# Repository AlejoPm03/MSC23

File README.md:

# Transformar MSC23 em sensor de tensão para a bateria

1. Soldar a placa normalmente usando o projeto que esta na branch voltage_sensor, 
não soldar compnentes que estão com X vermelho no esquematico

2. Soldar o conector na camada inversa a do projeto com as duas pernas centrais isoladas e distanciadas dos pads. 
Na proxima imagem tem exemplo, é recomendavel colocar algo para isolar o pino do pad (talvez o fenolite de uma PCB)

Deberia ficar algo parecido com a imagem:

3. No proximo passo serão soldados os componentes selecionados em montagem aerea

Deveria ficar algo parecido com a imagem:

# Documentos de Referência
[Simulação](design/analog_voltage_sensor.asc)
[Esquemático](exports/schematic.pdf/)

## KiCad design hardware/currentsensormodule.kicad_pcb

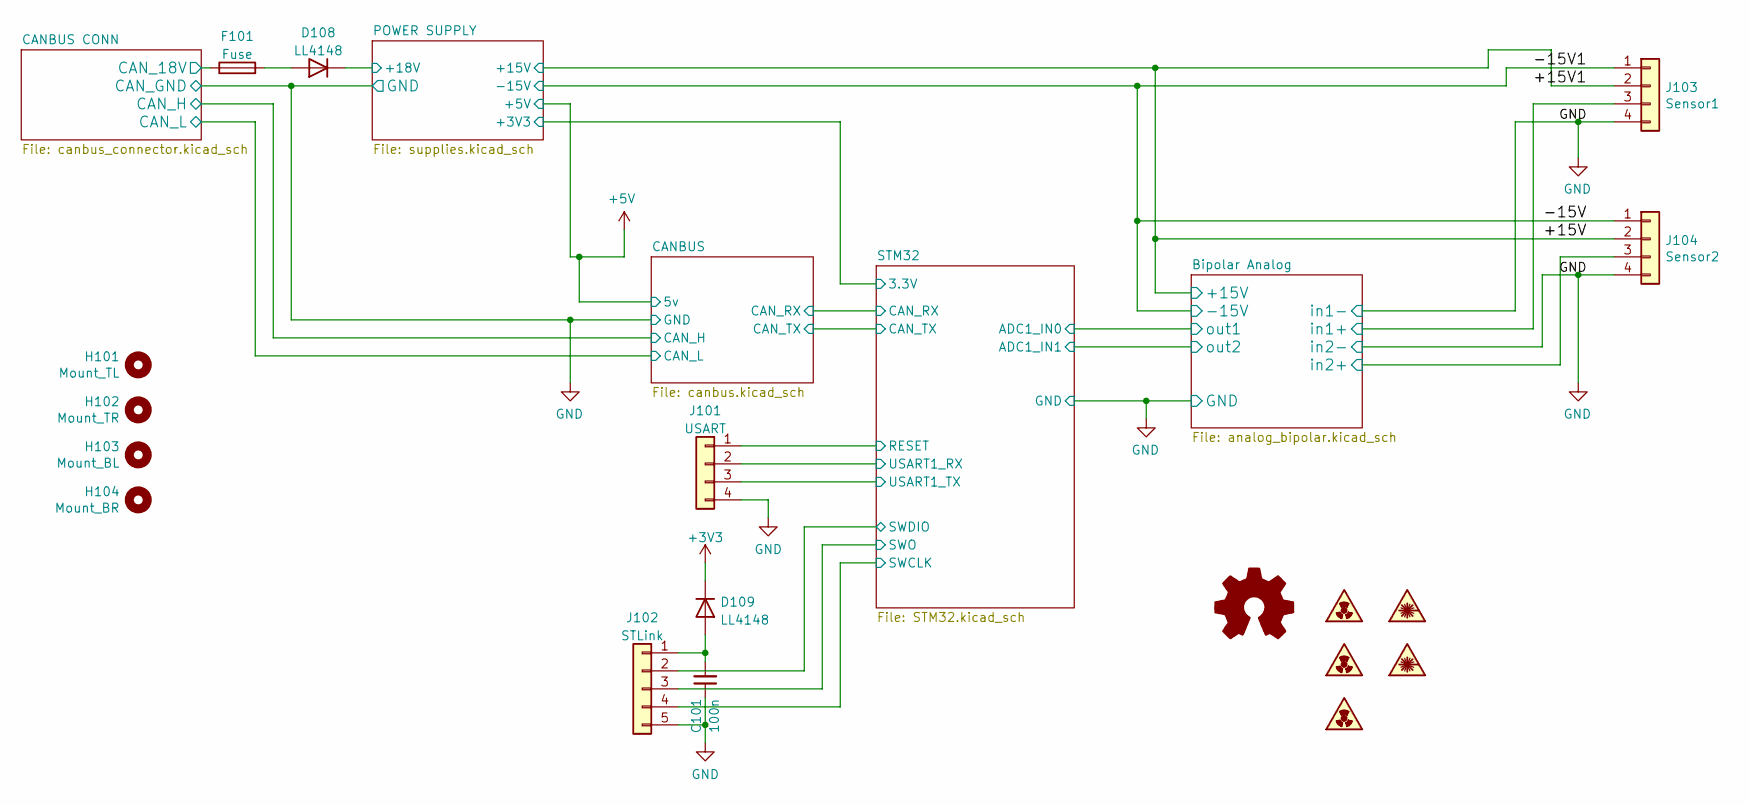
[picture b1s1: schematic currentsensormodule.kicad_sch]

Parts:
C101: 100n; C_0603_1608Metric_Pad1.08x0.95mm_HandSolder
D108, D109: LL4148; D_MiniMELF
F101: Fuse; Fuse_1812_4532Metric_Pad1.30x3.40mm_HandSolder
H101: Mount_TL; MountingHole_3.2mm_M3
H102: Mount_TR; MountingHole_3.2mm_M3
H103: Mount_BL; MountingHole_3.2mm_M3
H104: Mount_BR; MountingHole_3.2mm_M3
J101: USART; PinHeader_1x04_P2.54mm_Vertical_SMD_Pin1Left
J102: STLink; PinHeader_1x05_P2.54mm_Vertical_SMD_Pin1Left
J103: Sensor1; PhoenixContact_MSTBA_2,5_4-G-5,08_1x04_P5.08mm_Horizontal
J104: Sensor2; PhoenixContact_MSTBA_2,5_4-G-5,08_1x04_P5.08mm_Horizontal
LOGO101: Logo_Open_Hardware_Small; OSHW-Logo2_7.3x6mm_SilkScreen
SYM101, SYM103: SYM_Radioactive_Radiation_Small; symbol_logoZenite
SYM102, SYM104: SYM_LASER_Small; synbol_logoifsc
SYM105: SYM_Radioactive_Radiation_Small; symbol_naolavar

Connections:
+3V3: D109.1 (K); also elsewhere on the board
+15V: J103.2, J104.2; also elsewhere on the board
-15V: J103.1, J104.1; also elsewhere on the board
/Bipolar Analog/in1+: J103.3; also elsewhere on the board
/Bipolar Analog/in2+: J104.3; also elsewhere on the board
/CANBUS CONN/CAN_18V: F101.1; also elsewhere on the board
/POWER SUPPLY/+18V: D108.1 (K); also elsewhere on the board
/STM32/RESET: J101.1; also elsewhere on the board
/STM32/SWCLK: J102.4; also elsewhere on the board
/STM32/SWDIO: J102.2; also elsewhere on the board
/STM32/SWO: J102.3; also elsewhere on the board
/STM32/USART1_RX: J101.2; also elsewhere on the board
/STM32/USART1_TX: J101.3; also elsewhere on the board
GND: C101.1, J101.4, J102.5, J103.4, J104.4; also elsewhere on the board
unnamed: C101.2, D109.2 (A), J102.1
unnamed: D108.2 (A), F101.2

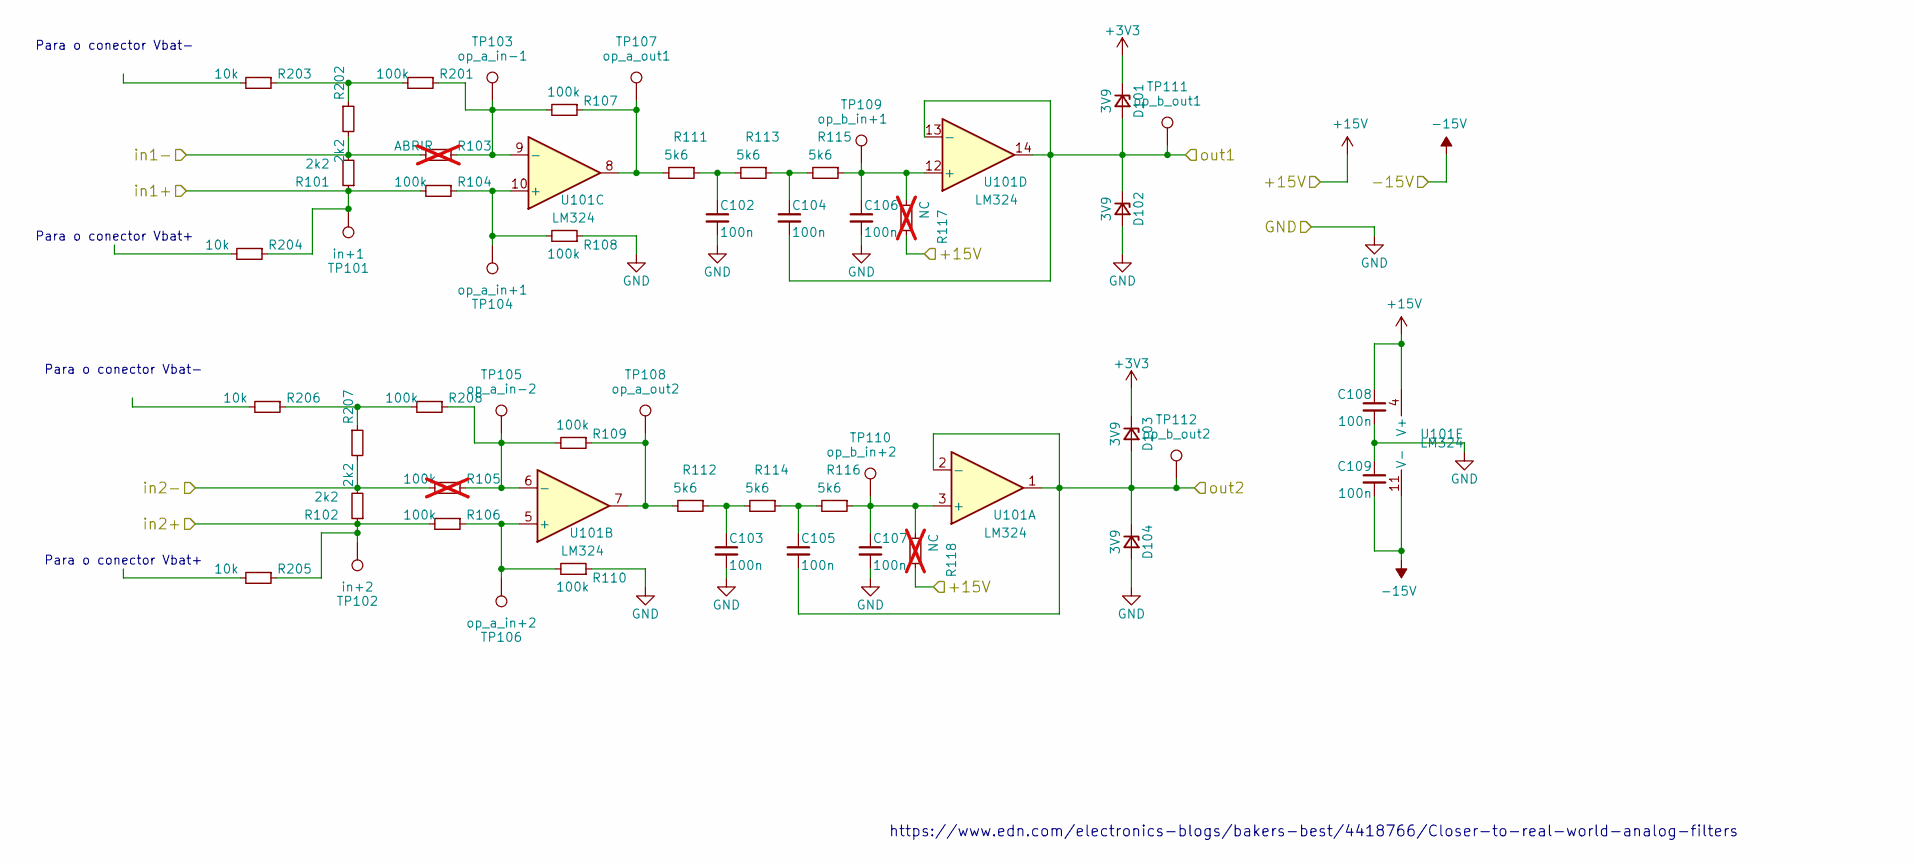
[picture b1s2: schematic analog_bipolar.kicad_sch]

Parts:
C102, C103, C104, C105, C106, C107, C108, C109: 100n; C_0603_1608Metric_Pad1.08x0.95mm_HandSolder
D101, D102, D103, D104: 3V9; D_MiniMELF_Handsoldering
R101, R102, R202, R207: 2k2; R_0603_1608Metric_Pad0.98x0.95mm_HandSolder
R103: ABRIR; R_0603_1608Metric_Pad0.98x0.95mm_HandSolder; not fitted
R104, R106, R107, R108, R109, R110, R201, R208: 100k; R_0603_1608Metric_Pad0.98x0.95mm_HandSolder
R105: 100k; R_0603_1608Metric_Pad0.98x0.95mm_HandSolder; not fitted
R111, R112, R113, R114, R115, R116: 5k6; R_0603_1608Metric_Pad0.98x0.95mm_HandSolder
R117, R118: NC; R_0603_1608Metric_Pad0.98x0.95mm_HandSolder; not fitted
R203, R204, R205, R206: 10k; R_0603_1608Metric_Pad0.98x0.95mm_HandSolder
TP101: in+1; TestPoint_Pad_2.0x2.0mm
TP102: in+2; TestPoint_Pad_2.0x2.0mm
TP103: op_a_in-1; TestPoint_Pad_2.0x2.0mm
TP104: op_a_in+1; TestPoint_Pad_2.0x2.0mm
TP105: op_a_in-2; TestPoint_Pad_2.0x2.0mm
TP106: op_a_in+2; TestPoint_Pad_2.0x2.0mm
TP107: op_a_out1; TestPoint_Pad_2.0x2.0mm
TP108: op_a_out2; TestPoint_Pad_2.0x2.0mm
TP109: op_b_in+1; TestPoint_Pad_2.0x2.0mm
TP110: op_b_in+2; TestPoint_Pad_2.0x2.0mm
TP111: op_b_out1; TestPoint_Pad_2.0x2.0mm
TP112: op_b_out2; TestPoint_Pad_2.0x2.0mm
U101: LM324; SOIC-14_3.9x8.7mm_P1.27mm

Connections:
+3V3: D101.1 (K), D103.1 (K); also elsewhere on the board
+15V: C108.1, R117.1, R118.1, U101.4 (V+); also elsewhere on the board
-15V: C109.2, U101.11 (V-); also elsewhere on the board
/Bipolar Analog/in1+: R101.1, R104.2, R204.1, TP101.1; also elsewhere on the board
/Bipolar Analog/in2+: R102.1, R106.2, R205.1, TP102.1; also elsewhere on the board
/Bipolar Analog/out1: C104.2, D101.2 (A), D102.1 (K), TP111.1, U101.13 (-), U101.14; also elsewhere on the board
/Bipolar Analog/out2: C105.2, D103.2 (A), D104.1 (K), TP112.1, U101.1, U101.2 (-); also elsewhere on the board
GND: C102.2, C103.2, C106.2, C107.2, C108.2, C109.1, D102.2 (A), D104.2 (A), R101.2, R102.2, R103.2, R105.2, R108.1, R110.1, R202.2, R207.2; also elsewhere on the board
unnamed: C102.1, R111.1, R113.2
unnamed: C103.1, R112.1, R114.2
unnamed: C104.1, R113.1, R115.2
unnamed: C105.1, R114.1, R116.2
unnamed: C106.1, R115.1, R117.2, TP109.1, U101.12 (+)
unnamed: C107.1, R116.1, R118.2, TP110.1, U101.3 (+)
unnamed: R103.1, R107.2, R201.1, TP103.1, U101.9 (-)
unnamed: R104.1, R108.2, TP104.1, U101.10 (+)
unnamed: R105.1, R109.2, R208.1, TP105.1, U101.6 (-)
unnamed: R106.1, R110.2, TP106.1, U101.5 (+)
unnamed: R107.1, R111.2, TP107.1, U101.8
unnamed: R109.1, R112.2, TP108.1, U101.7
unnamed: R201.2, R202.1, R203.1
unnamed: R206.1, R207.1, R208.2

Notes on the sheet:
Para o conector Vbat-
Para o conector Vbat+
https://www.edn.com/electronics-blogs/bakers-best/4418766/Closer-to-real-world-analog-filters

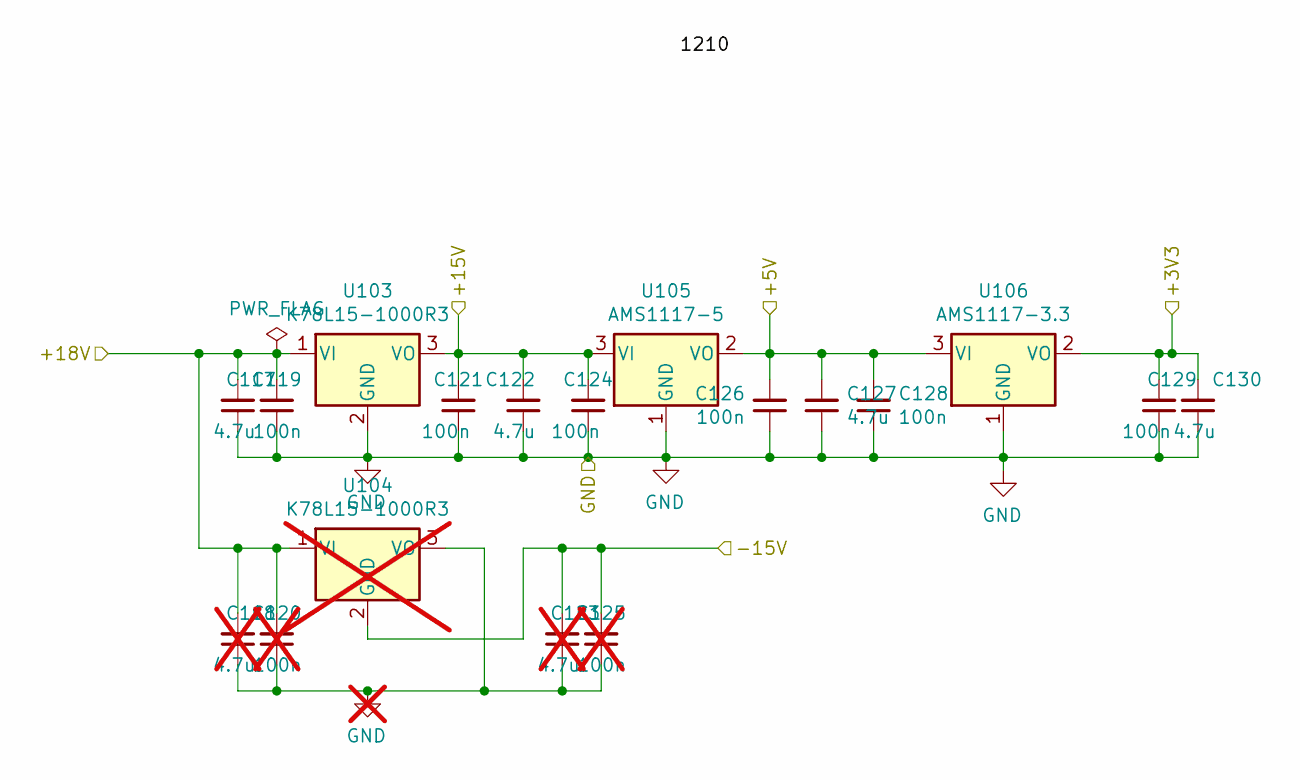
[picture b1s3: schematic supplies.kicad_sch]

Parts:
C117, C122, C127, C130: 4.7u; C_1206_3216Metric_Pad1.33x1.80mm_HandSolder
C118, C123: 4.7u; C_1206_3216Metric_Pad1.33x1.80mm_HandSolder; not fitted
C119, C121, C124, C126, C128, C129: 100n; C_0603_1608Metric_Pad1.08x0.95mm_HandSolder
C120, C125: 100n; C_0603_1608Metric_Pad1.08x0.95mm_HandSolder; not fitted
U103: K78L15-1000R3; TO-220-3_Horizontal_Tabless_SMD
U104: K78L15-1000R3; TO-220-3_Horizontal_Tabless_SMD; not fitted
U105: AMS1117-5; SOT-223-3_TabPin2
U106: AMS1117-3.3; SOT-223-3_TabPin2

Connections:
+3V3: C129.2, C130.2, U106.2 (VO); also elsewhere on the board
+5V: C126.2, C127.2, C128.2, U105.2 (VO), U106.3 (VI); also elsewhere on the board
+15V: C121.2, C122.2, C124.2, U103.3 (VO), U105.3 (VI); also elsewhere on the board
-15V: C123.2, C125.2, U104.2 (GND); also elsewhere on the board
/POWER SUPPLY/+18V: C117.2, C118.2, C119.2, C120.2, U103.1 (VI), U104.1 (VI); also elsewhere on the board
GND: C117.1, C118.1, C119.1, C120.1, C121.1, C122.1, C123.1, C124.1, C125.1, C126.1, C127.1, C128.1, C129.1, C130.1, U103.2 (GND), U104.3 (VO), U105.1 (GND), U106.1 (GND); also elsewhere on the board

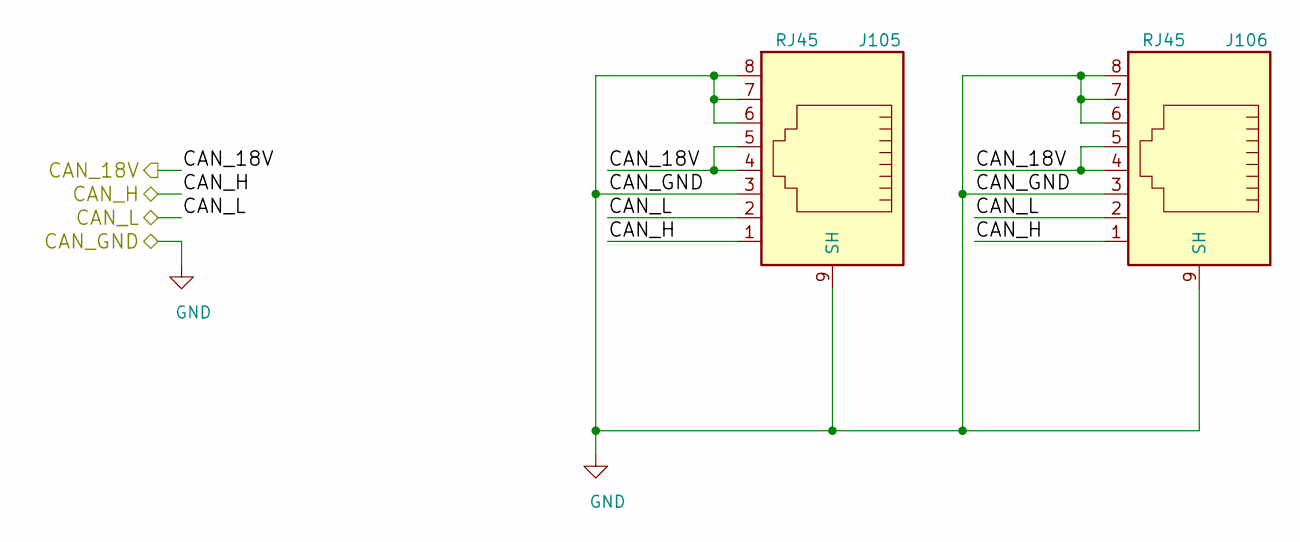
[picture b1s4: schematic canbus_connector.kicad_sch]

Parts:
J105, J106: RJ45; RJ45_YH59_01

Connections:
/CANBUS CONN/CAN_18V: J105.4, J105.5, J106.4, J106.5; also elsewhere on the board
/CANBUS CONN/CAN_H: J105.1, J106.1; also elsewhere on the board
/CANBUS CONN/CAN_L: J105.2, J106.2; also elsewhere on the board
GND: J105.3, J105.6, J105.7, J105.8, J105.9 (SH), J106.3, J106.6, J106.7, J106.8, J106.9 (SH); also elsewhere on the board

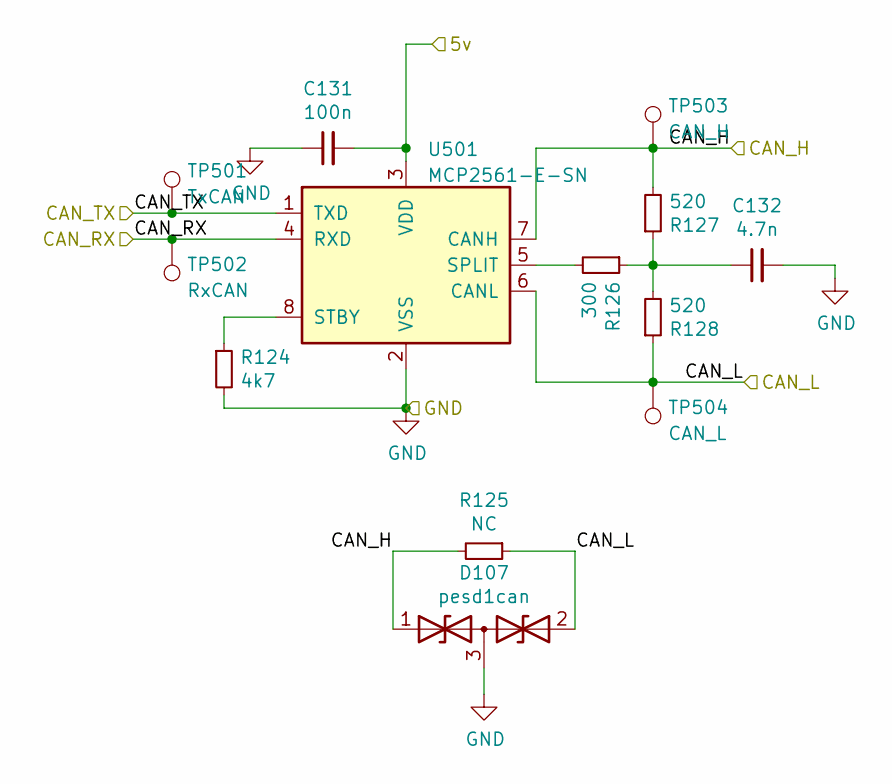
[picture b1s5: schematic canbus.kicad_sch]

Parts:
C131: 100n; C_0603_1608Metric_Pad1.08x0.95mm_HandSolder
C132: 4.7n; C_0603_1608Metric_Pad1.08x0.95mm_HandSolder
D107: pesd1can; SOT-23
R124: 4k7; R_0603_1608Metric_Pad0.98x0.95mm_HandSolder
R125: NC; R_0603_1608Metric_Pad0.98x0.95mm_HandSolder
R126: 300; R_0603_1608Metric_Pad0.98x0.95mm_HandSolder
R127, R128: 520; R_0603_1608Metric_Pad0.98x0.95mm_HandSolder
TP501: TxCAN; TestPoint_Pad_2.0x2.0mm
TP502: RxCAN; TestPoint_Pad_2.0x2.0mm
TP503: CAN_H; TestPoint_Pad_2.0x2.0mm
TP504: CAN_L; TestPoint_Pad_2.0x2.0mm
U501: MCP2561-E-SN; SOIC-8_3.9x4.9mm_P1.27mm

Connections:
+5V: C131.2, U501.3 (VDD); also elsewhere on the board
/CANBUS CONN/CAN_H: D107.1 (A1), R125.2, R127.2, TP503.1, U501.7 (CANH); also elsewhere on the board
/CANBUS CONN/CAN_L: D107.2 (A2), R125.1, R128.1, TP504.1, U501.6 (CANL); also elsewhere on the board
/CANBUS/CAN_RX: TP502.1, U501.4 (RXD); also elsewhere on the board
/CANBUS/CAN_TX: TP501.1, U501.1 (TXD); also elsewhere on the board
GND: C131.1, C132.2, D107.3 (common), R124.2, U501.2 (VSS); also elsewhere on the board
unnamed: C132.1, R126.1, R127.1, R128.2
unnamed: R124.1, U501.8 (STBY)
unnamed: R126.2, U501.5 (SPLIT)

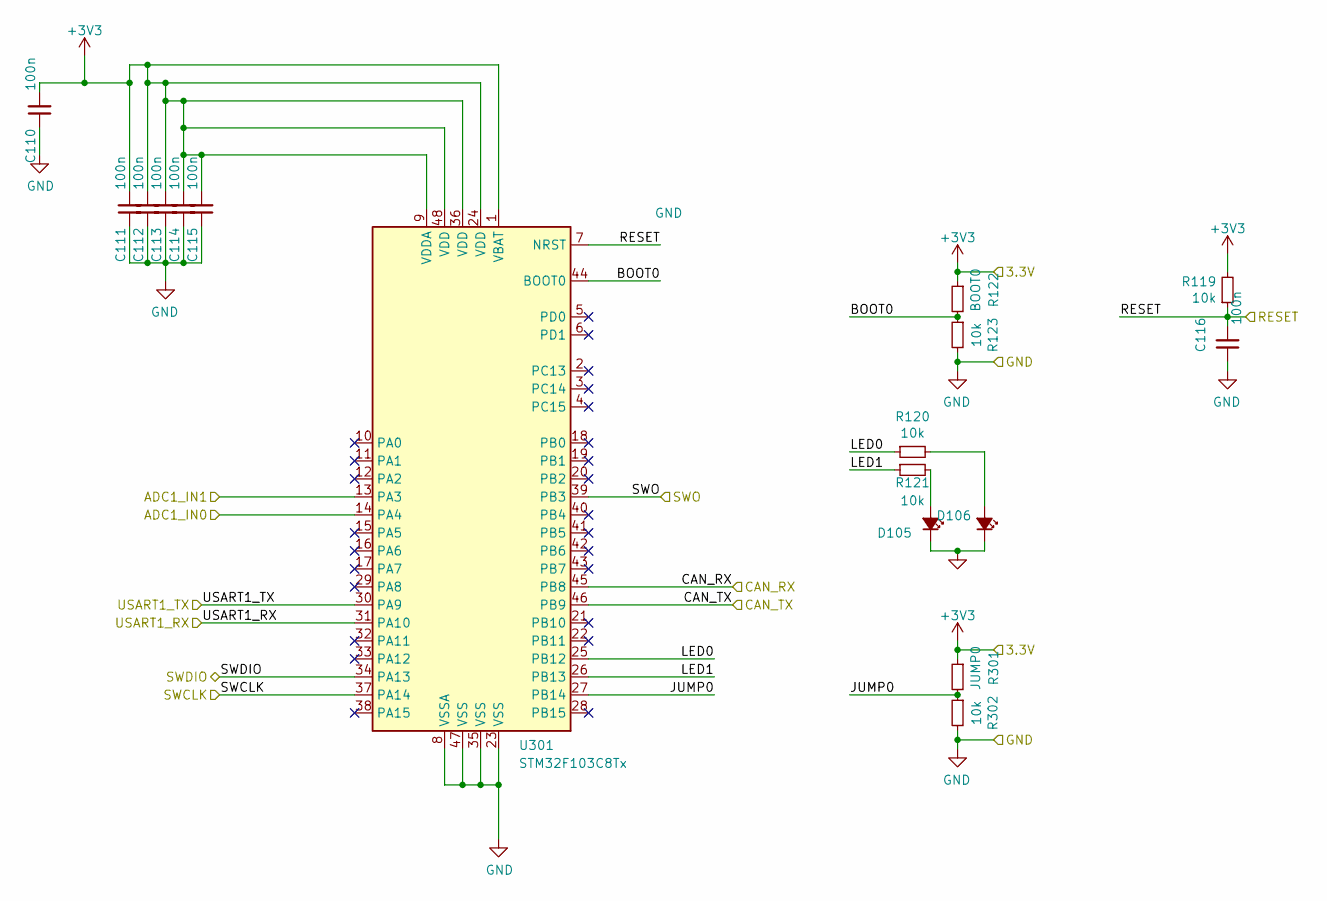
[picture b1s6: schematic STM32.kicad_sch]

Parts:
C110, C111, C112, C113, C114, C115, C116: 100n; C_0603_1608Metric_Pad1.08x0.95mm_HandSolder
D105, D106: LED_0805_2012Metric_Pad1.15x1.40mm_HandSolder
R119, R120, R121, R123, R302: 10k; R_0603_1608Metric_Pad0.98x0.95mm_HandSolder
R122: BOOT0; SolderJumper-2_P1.3mm_Open_RoundedPad1.0x1.5mm
R301: JUMP0; SolderJumper-2_P1.3mm_Open_RoundedPad1.0x1.5mm
U301: STM32F103C8Tx; LQFP-48_7x7mm_P0.5mm

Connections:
+3V3: C110.2, C111.2, C112.2, C113.2, C114.2, C115.2, R119.2, R122.1, R301.1, U301.1 (VBAT), U301.9 (VDDA), U301.24 (VDD), U301.36 (VDD), U301.48 (VDD); also elsewhere on the board
/Bipolar Analog/out1: U301.14 (PA4); also elsewhere on the board
/Bipolar Analog/out2: U301.13 (PA3); also elsewhere on the board
/CANBUS/CAN_RX: U301.45 (PB8); also elsewhere on the board
/CANBUS/CAN_TX: U301.46 (PB9); also elsewhere on the board
/STM32/BOOT0: R122.2, R123.1, U301.44 (BOOT0)
/STM32/JUMP0: R301.2, R302.1, U301.27 (PB14)
/STM32/LED0: R120.1, U301.25 (PB12)
/STM32/LED1: R121.1, U301.26 (PB13)
/STM32/RESET: C116.2, R119.1, U301.7 (NRST); also elsewhere on the board
/STM32/SWCLK: U301.37 (PA14); also elsewhere on the board
/STM32/SWDIO: U301.34 (PA13); also elsewhere on the board
/STM32/SWO: U301.39 (PB3); also elsewhere on the board
/STM32/USART1_RX: U301.31 (PA10); also elsewhere on the board
/STM32/USART1_TX: U301.30 (PA9); also elsewhere on the board
GND: C110.1, C111.1, C112.1, C113.1, C114.1, C115.1, C116.1, D105.1 (K), D106.1 (K), R123.2, R302.2, U301.8 (VSSA), U301.23 (VSS), U301.35 (VSS), U301.47 (VSS); also elsewhere on the board
unnamed: D105.2 (A), R121.2
unnamed: D106.2 (A), R120.2

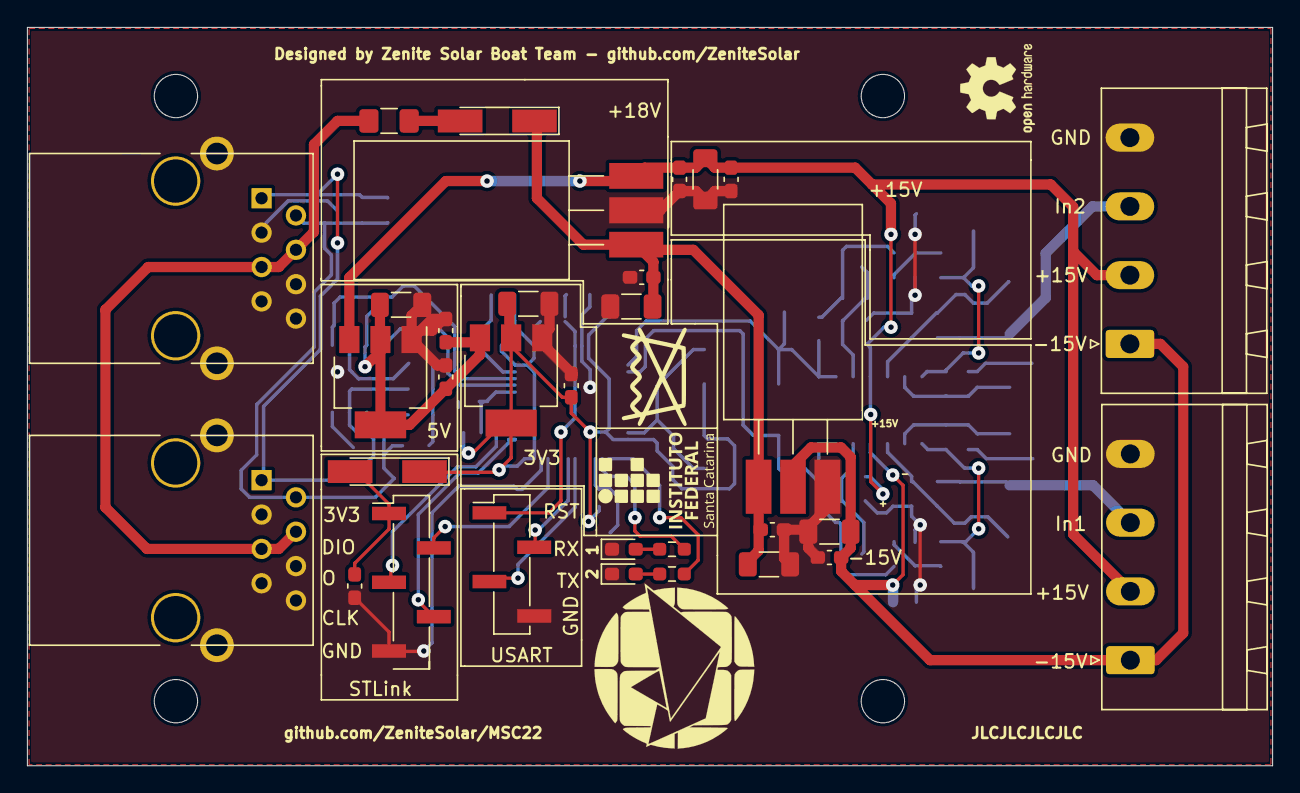
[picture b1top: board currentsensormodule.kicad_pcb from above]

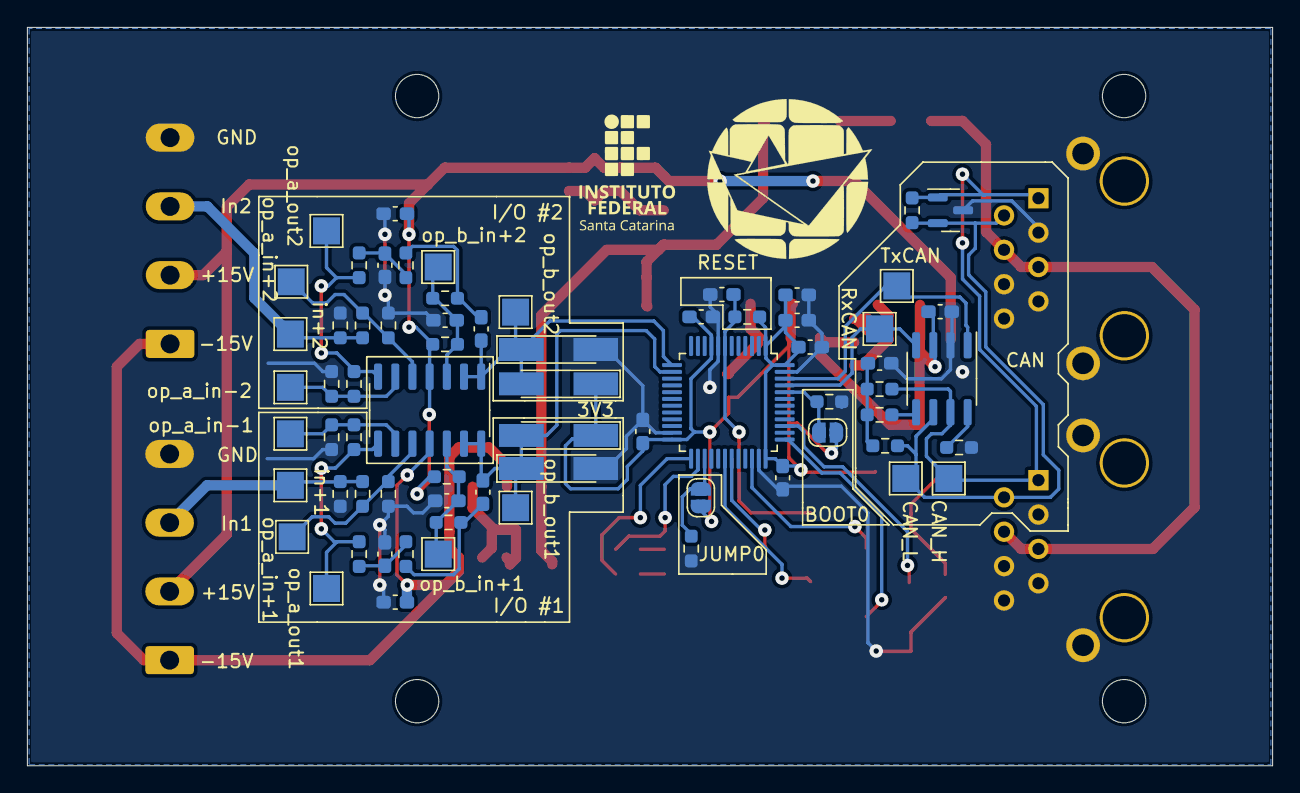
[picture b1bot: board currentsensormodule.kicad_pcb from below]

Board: 2 copper layers, 92.0 x 54.5 mm, 111 parts (71 on the bottom side), 44 nets.

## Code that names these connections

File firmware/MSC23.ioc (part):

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Mcu.Name=STM32F103C(8-B)Tx
Mcu.Package=LQFP48
Mcu.UserName=STM32F103C8Tx
PA10.Mode=Asynchronous
PA10.Signal=USART1_RX
PA13.Mode=Trace_Asynchronous_SW
PA13.Signal=SYS_JTMS-SWDIO
PA14.Mode=Trace_Asynchronous_SW
PA14.Signal=SYS_JTCK-SWCLK
PA3.GPIOParameters=GPIO_Label
PA3.GPIO_Label=Ibat
PA3.Signal=ADCx_IN3
PA4.Signal=ADCx_IN4
PA9.Mode=Asynchronous
PA9.Signal=USART1_TX
PB12.GPIOParameters=GPIO_Label
PB12.GPIO_Label=LED0
PB12.Signal=GPIO_Output
PB13.GPIOParameters=GPIO_Label
PB13.GPIO_Label=LED1
PB13.Signal=GPIO_Output
PB14.GPIOParameters=GPIO_Label
PB14.GPIO_Label=JUMP0
PB14.Signal=GPIO_Input
PB3.Mode=Trace_Asynchronous_SW
PB3.Signal=SYS_JTDO-TRACESWO
PB8.Mode=CAN_Activate
PB8.Signal=CAN_RX
PB9.Mode=CAN_Activate
PB9.Signal=CAN_TX
RCC.SYSCLKFreq_VALUE=56000000
RCC.SYSCLKSource=RCC_SYSCLKSOURCE_PLLCLK
board=custom

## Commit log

2023-07-01 temporary code for lic test
2023-07-01 Update gitignore
2024-06-28 changes for voltage sensor
2024-06-28 added references
2024-06-28 fix path
